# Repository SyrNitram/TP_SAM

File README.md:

Q13 : PB9 est tirée à la masse par la resistance de 100k car ce pin coeespond à BOOT0.
Lorsque ce pin est à 0 le boot s'effectue depuis la memoire flash si le bit de config nBOOT_SEL est à 0.

Q14 : L1, C5, C7 forment un filtre passe-bas. ce filtre permet d'éliminer les parasite eventuels sur l'alimenttion avant que la tension de sortie serve de reference à l'ADC du microcontrôleur (VDDA).

# Le reste
Q3 : La première page indique que Cin et Cout doivent être superieurs à 0.47uF. La page 3 donne une valeur typique de 1uF.

Q5 : Page 25.

Q6 : CS est l'entrée chip select active à l'état bas. elle permet d'activer la communication spi avec ce composant.

Q7 : La broche LDAC permet de déclencher le changement de la tension de sortie quand l'entrée est à 0.

Q8 : Le signal MISO n'est pas utilisé car le MCP ne revoit pas d'information au microcontrôleur.

Q10 : Le pinout du connecteur SWD se trouve dans la documentation du STlink page 26.

# Affectation des empreintes

Q3 : Il s'agit de la taille du composant en dixième de pouce (ex : 0805 = 0.08 x 0.05 in).

Q4 : 	LQFP : Low Profile Quad Flat Package, est un type de boîtier de circuit intégré destiné à être directement soudé sur circuit imprimé.
	SOT : Small Outline Transistor, c'est un package fréquement utilisé pour les régulateurs de tension.
	SOIC : Small Outline Integrated Circuit, ce package est equivalent au boitier DIP mais est quasiment deux fois plus petit.
	
# LED simple

2. On souhaite une frequence de PWM de 1kHz avec une résolution de 8bits soit 256 valeurs. L'horloge choisie est à 16MHz, on sait que l'on veut un ARR de 255, on en deduit la valeur du prescaler PSC = 16000/256 = 62,5 . On choisis PSC = 63. 

#LED avec timer

3. PSC vaut 16 pour obtenir un compteur à 1MHz, on choisis ensuite un ARR de 1000 pour que le compteur se reset toutes les ms. on ective ensuite l'interruption sur reset.

6. La routine se trouve dans la fonction void TIM21_IRQHandler(void) dans stm32l0xx_it.c,elle est vide.

7. Il manque la remise à zero du flag d'interruption

8. l'interruption va se declencher en boucle si le flag n'est pas remis à 0.

9. Il faut remettre à 0 le flag.

#UART

5. La variable envoyer n'est pas le pointeur vers la variable mais la variable elle-même.

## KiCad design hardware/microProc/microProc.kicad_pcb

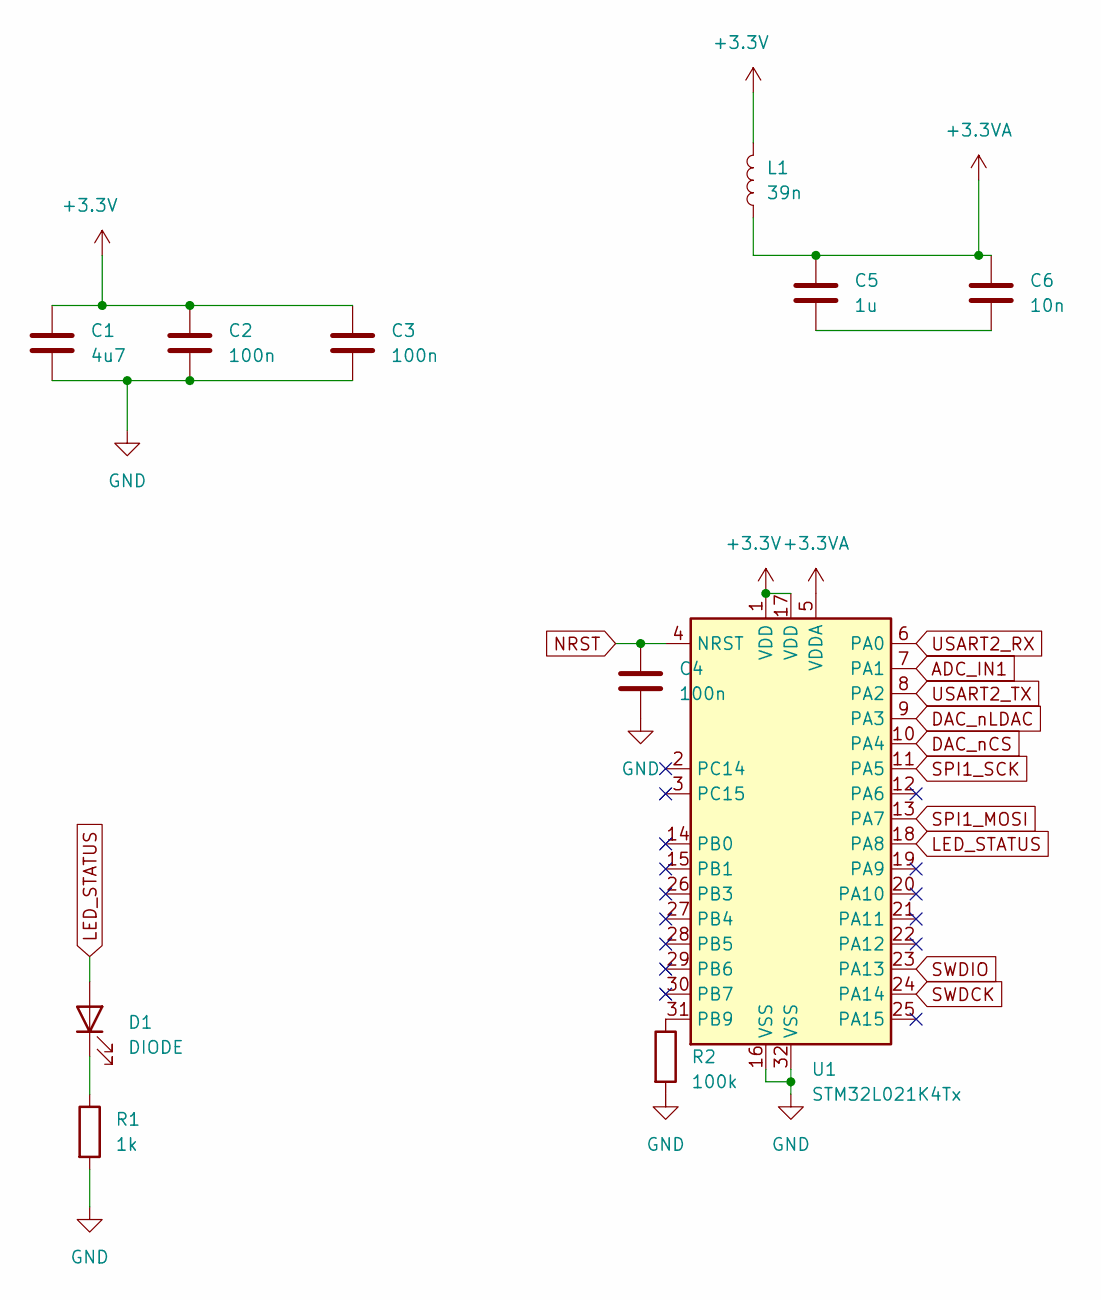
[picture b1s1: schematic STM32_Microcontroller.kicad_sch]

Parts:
C1: 4u7; C_0805_2012Metric_Pad1.18x1.45mm_HandSolder
C2, C3, C4: 100n; C_0805_2012Metric_Pad1.18x1.45mm_HandSolder
C5: 1u; C_0805_2012Metric_Pad1.18x1.45mm_HandSolder
C6: 10n; C_0805_2012Metric_Pad1.18x1.45mm_HandSolder
D1: DIODE; LED_0603_1608Metric_Pad1.05x0.95mm_HandSolder
L1: 39n; L_0805_2012Metric_Pad1.05x1.20mm_HandSolder
R1: 1k; R_0805_2012Metric_Pad1.20x1.40mm_HandSolder
R2: 100k; R_0805_2012Metric_Pad1.20x1.40mm_HandSolder
U1: STM32L021K4Tx; LQFP-32_7x7mm_P0.8mm

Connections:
+3.3VA: C5.1, C6.1, L1.1, U1.5 (VDDA)
ADC_IN1: U1.7 (PA1); also elsewhere on the board
DAC_nCS: U1.10 (PA4); also elsewhere on the board
DAC_nLDAC: U1.9 (PA3); also elsewhere on the board
GND: C1.2, C2.2, C3.2, C4.2, R1.2, R2.2, U1.16 (VSS), U1.32 (VSS); also elsewhere on the board
LED_STATUS: D1.2 (A), U1.18 (PA8)
NRST: C4.1, U1.4 (NRST); also elsewhere on the board
unnamed: C5.2, C6.2
unnamed: D1.1 (K), R1.1
unnamed: R2.1, U1.31 (PB9)
SPI1_MOSI: U1.13 (PA7); also elsewhere on the board
SPI1_SCK: U1.11 (PA5); also elsewhere on the board
SWDCK: U1.24 (PA14); also elsewhere on the board
SWDIO: U1.23 (PA13); also elsewhere on the board
USART2_RX: U1.6 (PA0); also elsewhere on the board
USART2_TX: U1.8 (PA2); also elsewhere on the board

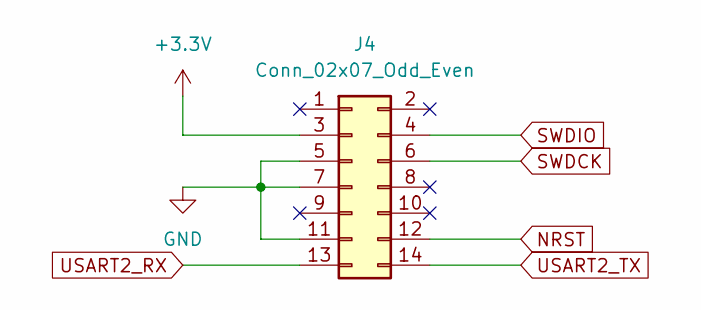
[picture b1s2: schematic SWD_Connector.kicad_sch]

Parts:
J4: Conn_02x07_Odd_Even; PinHeader_2x07_P1.27mm_Vertical_SMD

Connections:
GND: J4.5, J4.7, J4.11; also elsewhere on the board
NRST: J4.12; also elsewhere on the board
SWDCK: J4.6; also elsewhere on the board
SWDIO: J4.4; also elsewhere on the board
USART2_RX: J4.13; also elsewhere on the board
USART2_TX: J4.14; also elsewhere on the board

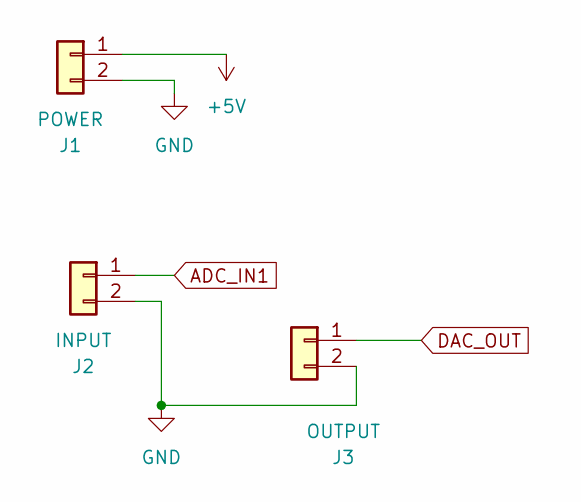
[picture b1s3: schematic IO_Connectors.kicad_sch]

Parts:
J1: POWER; JST_XH_B2B-XH-A_1x02_P2.50mm_Vertical
J2: INPUT; JST_XH_B2B-XH-A_1x02_P2.50mm_Vertical
J3: OUTPUT; JST_XH_B2B-XH-A_1x02_P2.50mm_Vertical

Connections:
+5V: J1.1; also elsewhere on the board
ADC_IN1: J2.1; also elsewhere on the board
DAC_OUT: J3.1; also elsewhere on the board
GND: J1.2, J2.2, J3.2; also elsewhere on the board

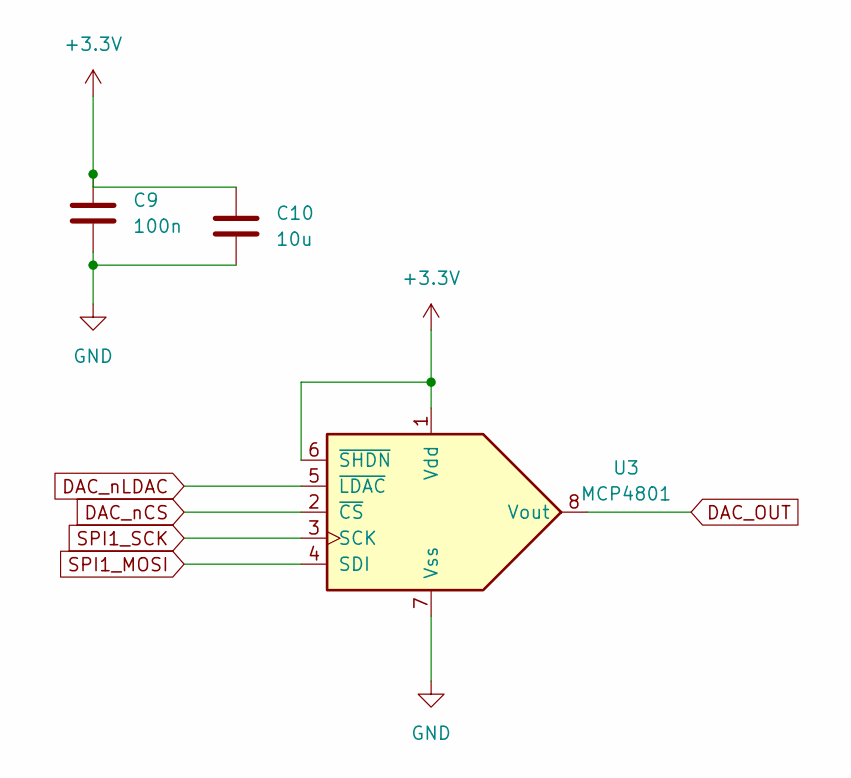
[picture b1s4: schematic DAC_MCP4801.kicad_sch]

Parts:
C9: 100n; C_0805_2012Metric_Pad1.18x1.45mm_HandSolder
C10: 10u; C_0805_2012Metric_Pad1.18x1.45mm_HandSolder
U3: MCP4801; SOIC-8_3.9x4.9mm_P1.27mm

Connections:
DAC_OUT: U3.8 (Vout); also elsewhere on the board
DAC_nCS: U3.2 (~CS); also elsewhere on the board
DAC_nLDAC: U3.5 (~LDAC); also elsewhere on the board
GND: C9.2, C10.2, U3.7 (Vss); also elsewhere on the board
SPI1_MOSI: U3.4 (SDI); also elsewhere on the board
SPI1_SCK: U3.3 (SCK); also elsewhere on the board

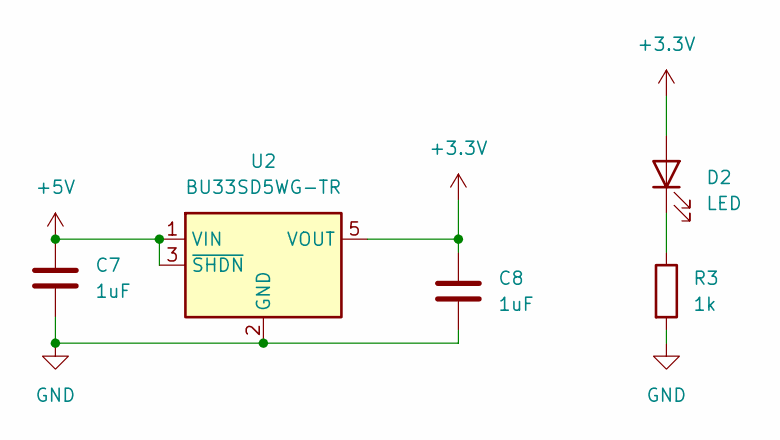
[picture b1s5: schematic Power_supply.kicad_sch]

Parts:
C7, C8: 1uF; C_0805_2012Metric_Pad1.18x1.45mm_HandSolder
D2: LED; LED_0603_1608Metric_Pad1.05x0.95mm_HandSolder
R3: 1k; R_0805_2012Metric_Pad1.20x1.40mm_HandSolder
U2: BU33SD5WG-TR; SOT-23-5

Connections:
+5V: C7.1, U2.1 (VIN), U2.3 (~SHDN); also elsewhere on the board
GND: C7.2, C8.2, R3.2, U2.2 (GND); also elsewhere on the board
unnamed: D2.1 (K), R3.1

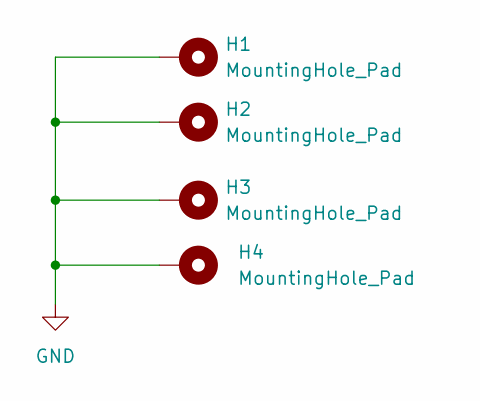
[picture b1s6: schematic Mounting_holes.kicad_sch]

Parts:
H1, H2, H3, H4: MountingHole_Pad; MountingHole_3.2mm_M3_Pad

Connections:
GND: H1.1, H2.1, H3.1, H4.1; also elsewhere on the board

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
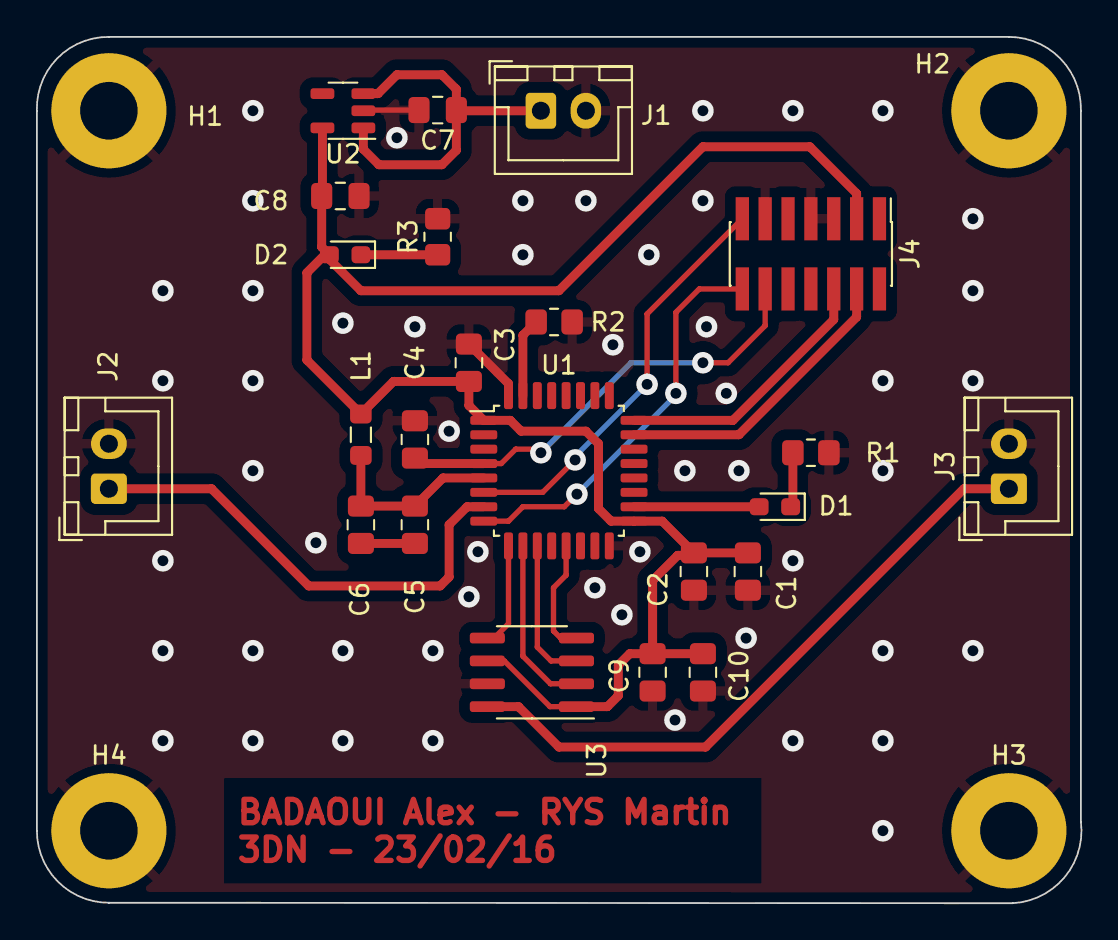
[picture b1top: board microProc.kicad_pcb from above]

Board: 2 copper layers, 58.0 x 48.1 mm, 27 parts (0 on the bottom side), 20 nets.

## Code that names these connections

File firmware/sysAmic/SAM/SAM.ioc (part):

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Mcu.Name=STM32L021K4Tx
Mcu.Package=LQFP32
Mcu.UserName=STM32L021K4Tx
PA0-CK_IN.Mode=Asynchronous
PA0-CK_IN.Signal=USART2_RX
PA1.Mode=IN1
PA1.Signal=ADC_IN1
PA13.Mode=Serial_Wire
PA13.Signal=SYS_SWDIO
PA14.Mode=Serial_Wire
PA14.Signal=SYS_SWCLK
PA2.Mode=Asynchronous
PA2.Signal=USART2_TX
PA3.GPIOParameters=GPIO_Label
PA3.GPIO_Label=DAC_nLDAC
PA3.Signal=GPIO_Output
PA4.GPIOParameters=GPIO_Label
PA4.GPIO_Label=DAC_nCS
PA4.Signal=GPIO_Output
PA5.Mode=TX_Only_Simplex_Unidirect_Master
PA5.Signal=SPI1_SCK
PA7.Mode=TX_Only_Simplex_Unidirect_Master
PA7.Signal=SPI1_MOSI
PA8.GPIOParameters=GPIO_Label
PA8.GPIO_Label=LED_STATUS
PA8.Signal=S_TIM2_CH1
RCC.HSE_VALUE=8000000
RCC.SYSCLKFreq_VALUE=16000000
RCC.SYSCLKSource=RCC_SYSCLKSOURCE_HSI
board=custom

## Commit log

2023-02-15 TEST
2023-02-15 REMOVED TEST
2023-02-15 Ajout des dossiers et des documentations
2023-02-15 Changement des noms pour plus de lisibilité
2023-02-15 Debut projet
    Init Cube MX et KICAD
2023-02-15 Added STLINK DS
2023-02-15 Changement
2023-02-15 Séparation des feuilles Kicad
2023-02-15 KICAD component ST32 microP
2023-02-15 Ajout de la feuille Power supply
2023-02-15 DAC MCP4801
2023-02-15 SWD connector
2023-02-15 IO Connector
2023-02-15 Ré-ajout de powersupply
2023-02-15 Correction nom powersupply
2023-02-15 RéRé-ajout power supply
2023-02-15 Suppression backup
2023-02-15 ERC verified, no error
2023-02-16 Remplacement de la doc du STlink
2023-02-16 Assigning Footprints
2023-02-16 v2 Assigning Footprints
2023-02-16 Added the mounting holes in Schematics
2023-02-16 Component placement
2023-02-16 Routage carte
2023-02-16 Final PCB
2023-02-16 Final Final PCB
2023-02-16 Added names to PCB
2023-03-10 Ajout du projet ST
2023-03-10 Led par interruption
2023-03-10 Ajout de la lisaison USART
